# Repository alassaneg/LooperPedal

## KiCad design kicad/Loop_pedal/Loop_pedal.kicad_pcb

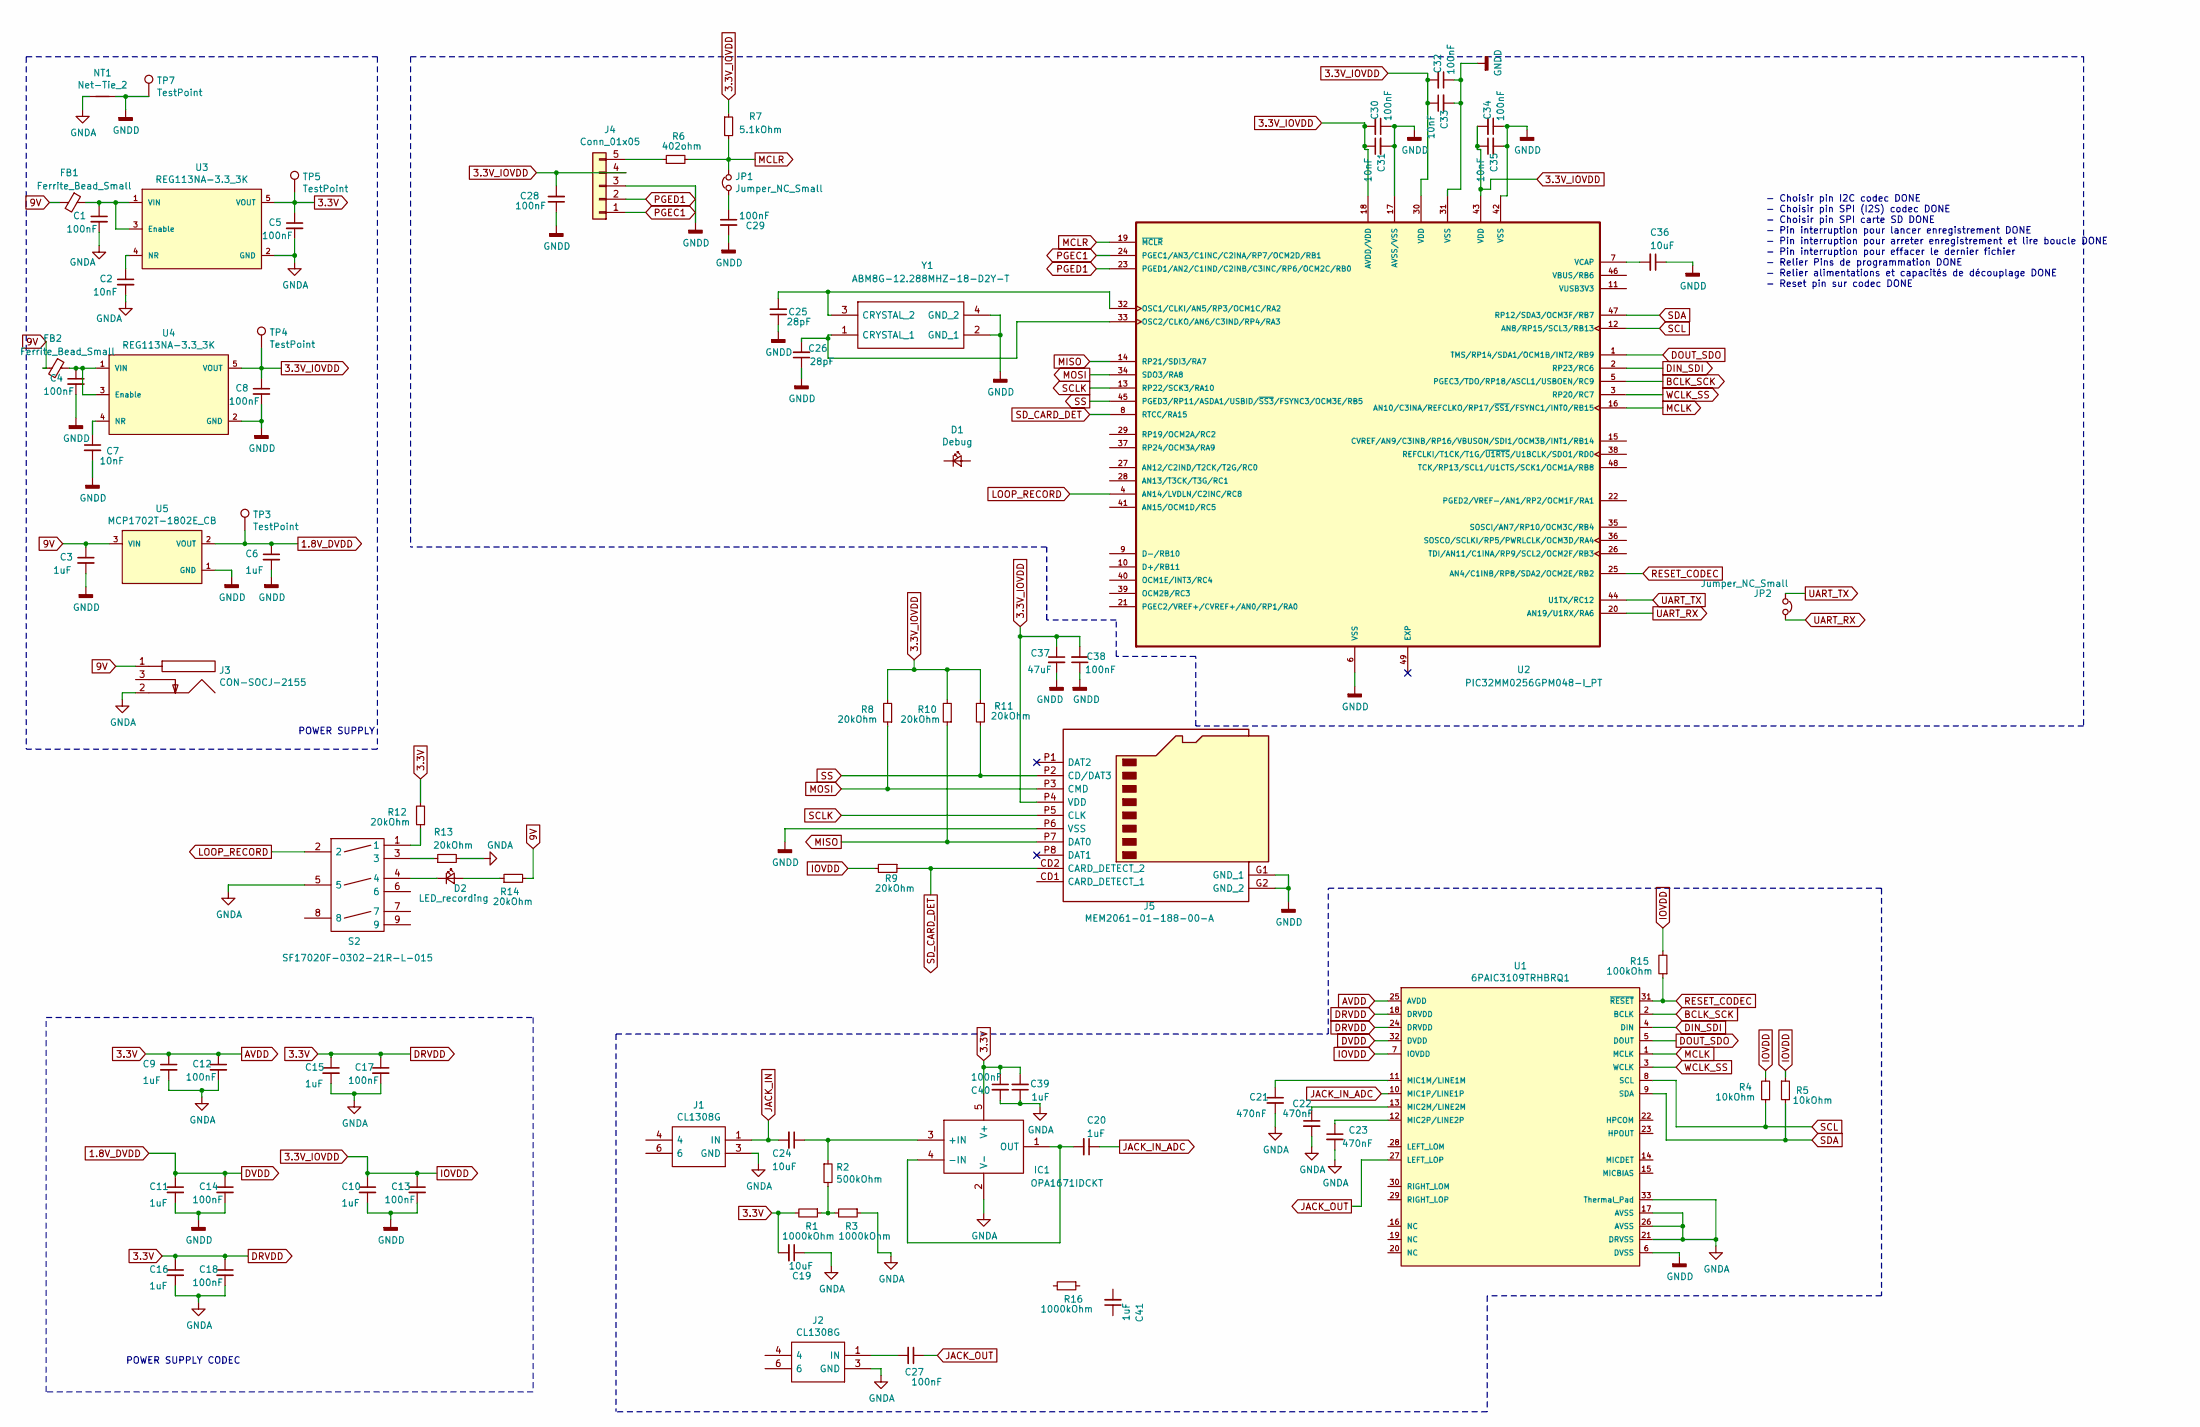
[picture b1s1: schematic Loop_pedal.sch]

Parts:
C1, C4, C5, C8, C27, C28, C29: 100nF; C_0805_2012Metric_Pad1.15x1.40mm_HandSolder
C2, C7: 10nF; C_0805_2012Metric_Pad1.15x1.40mm_HandSolder
C3, C6, C20, C41: 1uF; C_0805_2012Metric_Pad1.15x1.40mm_HandSolder
C9, C10, C11, C15, C16, C39: 1uF; C_0603_1608Metric_Pad1.05x0.95mm_HandSolder
C12, C13, C14, C17, C18, C30, C32, C34, C38, C40: 100nF; C_0603_1608Metric_Pad1.05x0.95mm_HandSolder
C19, C24: 10uF; C_0805_2012Metric_Pad1.15x1.40mm_HandSolder
C21, C22, C23: 470nF; C_0603_1608Metric_Pad1.05x0.95mm_HandSolder
C25, C26: 28pF; C_0603_1608Metric_Pad1.05x0.95mm_HandSolder
C31, C33, C35: 10nF; C_0603_1608Metric_Pad1.05x0.95mm_HandSolder
C36: 10uF; C_0603_1608Metric_Pad1.05x0.95mm_HandSolder
C37: 47uF; C_0805_2012Metric_Pad1.15x1.40mm_HandSolder
D1: Debug; LED_0805_2012Metric_Pad1.15x1.40mm_HandSolder
D2: LED_recording; LED_0805_2012Metric_Pad1.15x1.40mm_HandSolder
FB1, FB2: Ferrite_Bead_Small; L_0805_2012Metric_Pad1.15x1.40mm_HandSolder
IC1: OPA1671IDCKT; SOT65P210X110-5N; Manufacturer_Part_Number OPA1671IDCKT; Mouser Part Number 595-OPA1671IDCKT
J1, J2: CL1308G; Manufacturer_Part_Number CL1308G; Farnell Part Number 2766190
J3: CON-SOCJ-2155; CONSOCJ2155; Manufacturer_Part_Number CON-SOCJ-2155; Mouser Part Number 992-CON-SOCJ-2155
J4: Conn_01x05; PinHeader_1x05_P2.54mm_Vertical
J5: MEM2061-01-188-00-A; MEM20610118800A; Manufacturer_Part_Number MEM2061-01-188-00-A
JP1, JP2: Jumper_NC_Small; PinHeader_1x02_P2.54mm_Vertical
NT1: Net-Tie_2; NetTie-2_SMD_Pad2.0mm
R1, R3, R16: 1000kOhm; R_0805_2012Metric_Pad1.15x1.40mm_HandSolder
R2: 500kOhm; R_0805_2012Metric_Pad1.15x1.40mm_HandSolder
R4, R5: 10kOhm; R_0603_1608Metric_Pad1.05x0.95mm_HandSolder
R6: 402ohm; R_0805_2012Metric_Pad1.15x1.40mm_HandSolder
R7: 5.1kOhm; R_0805_2012Metric_Pad1.15x1.40mm_HandSolder
R8, R9, R10, R11, R12, R13, R14: 20kOhm; R_0805_2012Metric_Pad1.15x1.40mm_HandSolder
R15: 100kOhm; R_0603_1608Metric_Pad1.05x0.95mm_HandSolder
S2: SF17020F-0302-21R-L-015; SF17020F030221RL015; Mouser Part Number 107-SF17020F-32-21RL
TP3, TP4, TP7: TestPoint; TestPoint_Pad_D1.0mm
TP5: TestPoint; TestPoint_Pad_D2.0mm
U1: 6PAIC3109TRHBRQ1; Texas_Instruments-RHB0032A-0-0-0; mouser part number 595-6PAIC3109TRHBRQ1; digikey description AUTOMOTIVE LOW-POWER 96KHZ MONO
U2: PIC32MM0256GPM048-I_PT; QFP50P900X900X120-49N; PARTREV C
U3, U4: REG113NA-3.3_3K; Texas_Instruments-DBV0005A-0-0-IPC_A; dropout voltage 250mV; output voltage 3.3V; mouser part number 595-REG113NA-3.3/3K; digikey description IC REG LINEAR 3.3V 400MA SOT23-5
U5: MCP1702T-1802E_CB; Microchip-MCP1702T-1802E_CB-Level_A
Y1: ABM8G-12.288MHZ-18-D2Y-T; ABM8G48000MHZ18D2YT; Manufacturer_Part_Number ABM8G-12.288MHZ-18-D2Y-T; Mouser Part Number 815-ABM8G-12.2-18D2Y

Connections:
1.8V_DVDD: C6.1, C11.1, C14.1, TP3.1, U1.32 (DVDD), U5.2 (VOUT)
3.3V: C5.1, C9.1, C12.1, C15.1, C16.1, C17.1, C18.1, C19.2, C39.2, C40.1, IC1.5 (V+), R1.2, R12.2, TP5.1, U1.18 (DRVDD), U1.24 (DRVDD), U1.25 (AVDD), U3.5 (VOUT)
3.3V_IOVDD: C8.1, C10.1, C13.1, C28.2, C30.2, C31.1, C32.2, C33.1, C34.2, C35.1, C37.1, C38.2, J4.4, J5.P4 (VDD), R4.2, R5.1, R7.1, R8.2, R9.2, R10.2, R11.1, R15.2, TP4.1, U1.7 (IOVDD), U2.18 (AVDD/VDD), U2.30 (VDD), U2.43 (VDD), U4.5 (VOUT)
9V: C3.1, FB1.2, FB2.2, J3.1, R14.2, U5.3 (VIN)
BCLK_SCK: U1.2 (BCLK), U2.5 (PGEC3/TDO/RP18/ASCL1/USBOEN/RC9)
DIN_SDI: U1.4 (DIN), U2.2 (RP23/RC6)
DOUT_SDO: U1.5 (DOUT), U2.1 (TMS/RP14/SDA1/OCM1B/INT2/RB9)
GNDA: C1.2, C2.2, C5.2, C9.2, C12.2, C15.2, C16.2, C17.2, C18.2, C19.1, C21.2, C22.2, C23.2, C39.1, C40.2, IC1.2 (V-), J1.3 (GND), J2.3 (GND), J3.2, NT1.1, R3.1, R13.2, S2.5, U1.17 (AVSS), U1.21 (DRVSS), U1.26 (AVSS), U1.33 (Thermal_Pad), U3.2 (GND)
GNDD: C3.2, C4.2, C6.2, C7.2, C8.2, C10.2, C11.2, C13.2, C14.2, C25.1, C26.1, C28.1, C29.2, C30.1, C31.2, C32.1, C33.2, C34.1, C35.2, C36.1, C37.2, C38.1, J4.3, J5.G1 (GND_1), J5.G2 (GND_2), J5.P6 (VSS), NT1.2, TP7.1, U1.6 (DVSS), U2.6 (VSS), U2.17 (AVSS/VSS), U2.31 (VSS), U2.42 (VSS), U4.2 (GND), U5.1 (GND), Y1.2 (GND_1), Y1.4 (GND_2)
JACK_IN: C24.2, J1.1 (IN)
JACK_IN_ADC: C20.1, U1.10 (MIC1P/LINE1P)
JACK_OUT: C27.1, U1.27 (LEFT_LOP)
LOOP_RECORD: S2.2, U2.4 (AN14/LVDLN/C2INC/RC8)
MCLK: U1.1 (MCLK), U2.16 (AN10/C3INA/REFCLKO/RP17/~SS1~/FSYNC1/IN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)
MCLR: JP1.2, R6.2, R7.2, U2.19 (~MCLR)
MISO: J5.P7 (DAT0), R10.1, U2.14 (RP21/SDI3/RA7)
MOSI: J5.P3 (CMD), R8.1, U2.34 (SDO3/RA8)
unnamed: C1.1, FB1.1, U3.1 (VIN), U3.3 (Enable)
unnamed: C2.1, U3.4 (NR)
unnamed: C4.1, FB2.1, U4.1 (VIN), U4.3 (Enable)
unnamed: C7.1, U4.4 (NR)
unnamed: C20.2, IC1.1 (OUT), IC1.4 (-IN)
unnamed: C21.1, U1.11 (MIC1M/LINE1M)
unnamed: C22.1, U1.13 (MIC2M/LINE2M)
unnamed: C23.1, U1.12 (MIC2P/LINE2P)
unnamed: C24.1, IC1.3 (+IN), R2.1
unnamed: C25.2, U2.32 (OSC1/CLKI/AN5/RP3/OCM1C/RA2), Y1.3 (CRYSTAL_2)
unnamed: C26.2, U2.33 (OSC2/CLKO/AN6/C3IND/RP4/RA3), Y1.1 (CRYSTAL_1)
unnamed: C27.2, J2.1 (IN)
unnamed: C29.1, JP1.1
unnamed: C36.2, U2.7 (VCAP)
unnamed: D2.1 (K), S2.4
unnamed: D2.2 (A), R14.1
unnamed: J4.5, R6.1
unnamed: R1.1, R2.2, R3.2
unnamed: R12.1, S2.1
unnamed: R13.1, S2.3
PGEC1: J4.1, U2.24 (PGEC1/AN3/C1INC/C2INA/RP7/OCM2D/RB1)
PGED1: J4.2, U2.23 (PGED1/AN2/C1IND/C2INB/C3INC/RP6/OCM2C/R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)
RESET_CODEC: R15.1, U1.31 (~RESET~), U2.25 (AN4/C1INB/RP8/SDA2/OCM2E/RB2)
SCL: R4.1, U1.8 (SCL), U2.12 (AN8/RP15/SCL3/RB13)
SCLK: J5.P5 (CLK), U2.13 (RP22/SCK3/RA10)
SDA: R5.2, U1.9 (SDA), U2.47 (RP12/SDA3/OCM3F/RB7)
SD_CARD_DET: J5.CD2 (CARD_DETECT_2), R9.1, U2.8 (RTCC/RA15)
SS: J5.P2 (CD/DAT3), R11.2, U2.45 (PGED3/RP11/ASDA1/USBID/~SS3~/FSYNC3/OCM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)
UART_RX: JP2.2, U2.20 (AN19/U1RX/RA6)
UART_TX: JP2.1, U2.44 (U1TX/RC12)
WCLK_SS: U1.3 (WCLK), U2.3 (RP20/RC7)

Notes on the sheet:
POWER SUPPLY
- Choisir pin I2C codec DONE - Choisir pin SPI (I2S) codec DONE - Choisir pin SPI carte SD DONE - Pin interruption pour lancer enregistrement DONE - Pin interruption pour arreter enregistrement et lire boucle DONE - Pin interruption pour effacer le dernier fichier - Relier Pins de programmation DON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
POWER SUPPLY CODEC

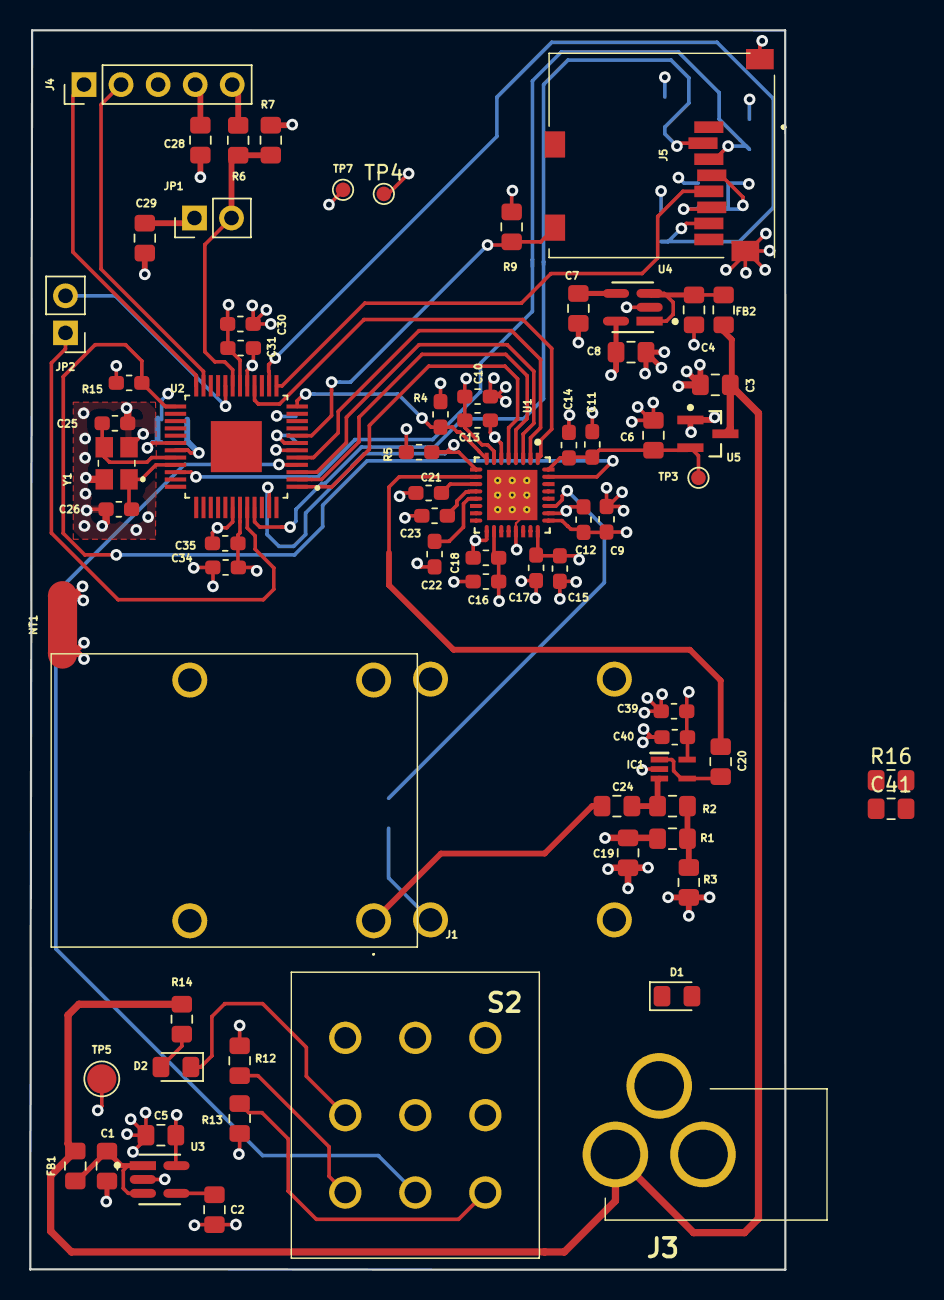
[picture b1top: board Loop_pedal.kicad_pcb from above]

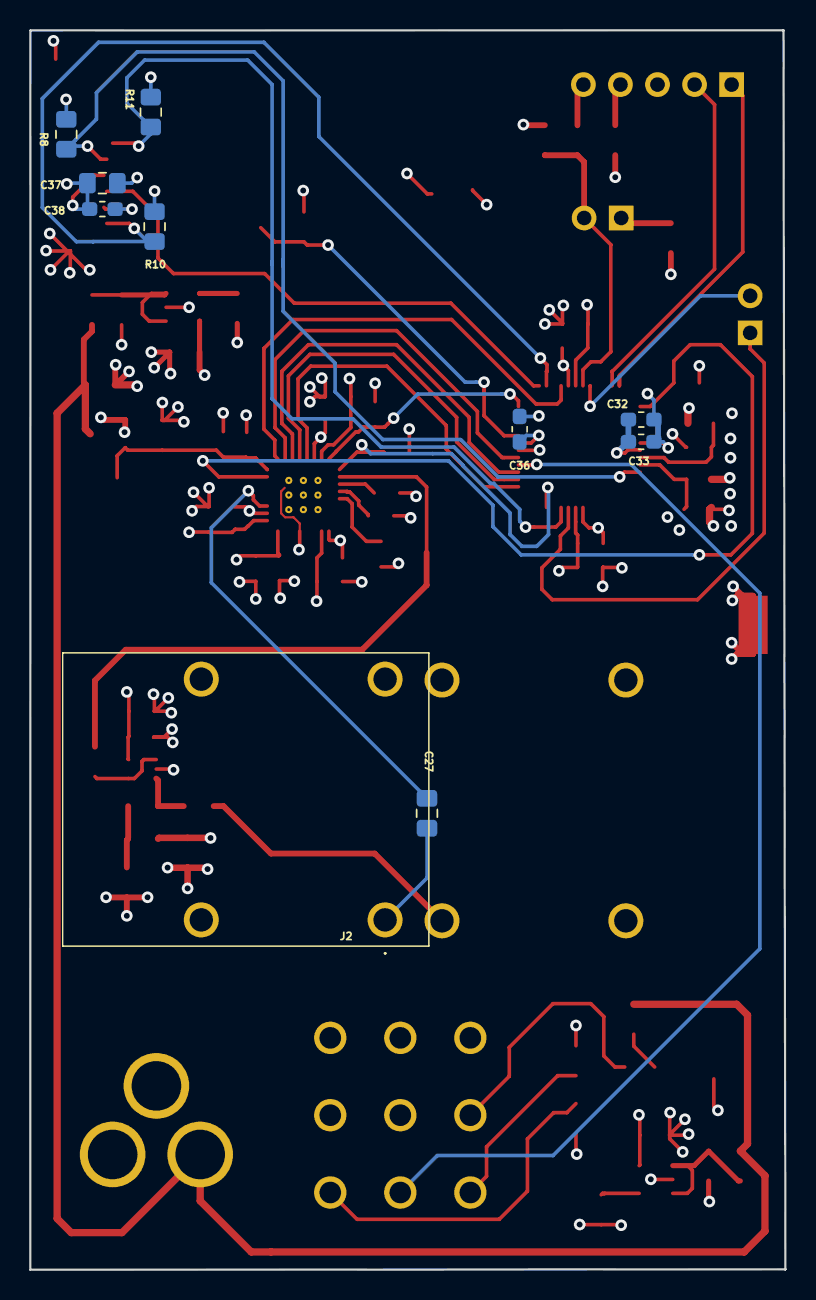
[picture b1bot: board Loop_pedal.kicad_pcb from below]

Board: 4 copper layers, 51.8 x 85.0 mm, 81 parts (10 on the bottom side), 48 nets.

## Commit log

2021-03-29 Premier depot new file: BOM/BOM_JLCSMT.xlsx new file: BOM/CPL_JLCSMT.xlsx new file: Simulation/ad8476.cir new file: kicad/Loop_pedal/Loop_pedal-cache.lib new file: kicad/Loop_pedal/Loop_pedal.bak new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
